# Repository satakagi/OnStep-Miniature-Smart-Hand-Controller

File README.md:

# OnStep-Miniature-Smart-Hand-Controller

## About
This is a much smaller design of the [Smart Hand Controller (SHC)](https://onstep.groups.io/g/main/wiki/7152) for [OnStep](https://onstep.groups.io/g/main)*1.
It is based on the [OnStep ESP32 Smart Hand Controller](https://baheyeldin.com/astronomy/onstep-esp32-smart-hand-controller-shc.html) circuit.

Therefore, the firmware is exactly the same as the ESP32 SHC, see the section Installing the Platform - For the ESP32 SHC on [The Smart Hand Controller (SHC)](https://onstep.groups.io/g/main/wiki/7152) page.

*1: OnStep is an open source GoTo motor drive for telescope mounts

## Parts List

* [DOIT ESP32 DEVKIT V1](https://www.amazon.com/s?k=DOIT+ESP32+DEVKIT+V1)
  * Note: Unlike the original ESP32 SHC, this design uses the DOIT ESP32 DEVKIT V1 with 30 pins.
* PCB ( refer to [kicad](kicad/) directory )
* [0.96" SSD1306 OLED Module](https://www.amazon.com/s?k=0.96+ssd1306+oled)
  * Note: Stick tape on the back side for insulation.
* Modular Jack 6P6C x 2
  * The plastic pins for fixing the jacks should be cut out.
* 7 Resistor Network (2K ohm)
* 4 Resistor Network (2K ohm)
* 2.54mm Header Pins 15pin F x 2, 4pin M, 2pin M 
* Momentary Tact Button Switches 0.2" x 0.24" x 7
  * Buttons would need to be at least 0.24" long.
* Case ( refer to [miniSHCcase.stl](miniSHCcase.stl) )
  * The example on this page were produced using the MSLA LCD 3d printer.

## Photos of the interior structure

Tape is attached to the back of the OLED module for insulation.
|  - |  -  |
| ---- | ---- |
|    |    |
|  <br>To avoid interference with the OLED, the leads protruding from the through-holes are trimmed.  |  <br>Attach a pad to the lid to hold the board in place and close the lid. (In this picture, the lid is fastened with tape.)   |

## License
This is licensed under the [TAPR Open Hardware License](https://tapr.org/the-tapr-open-hardware-license/), one of the well-known open-source hardware licenses.

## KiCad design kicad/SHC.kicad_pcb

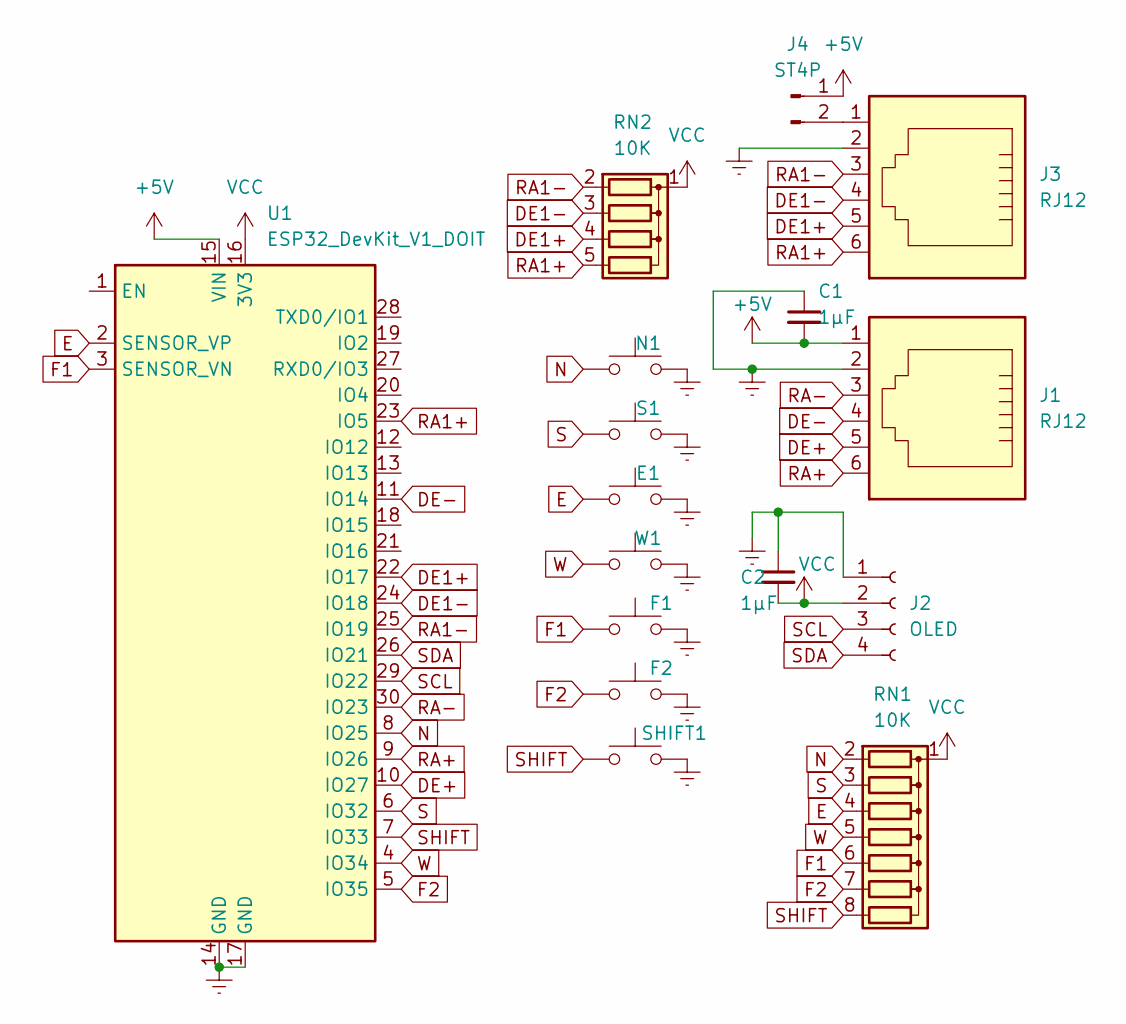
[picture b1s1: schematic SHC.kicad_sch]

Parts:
C1, C2: 1μF; C_Disc_D5.0mm_W2.5mm_P2.50mm
E1: SW_Push; SW_PUSH_6mm_H8mm
F1, F2: SW_Push; SW_PUSH_6mm_H8mm
J1, J3: RJ12; RJ25_Wayconn_MJEA-660X1_Horizontal_NoSupport
J2: OLED; PinHeader_1x04_P2.54mm_Vertical
J4: ST4P; PinHeader_1x02_P2.54mm_Vertical
N1: SW_Push; SW_PUSH_6mm_H8mm
RN1: 10K; R_Array_SIP8
RN2: 10K; R_Array_SIP5
S1: SW_Push; SW_PUSH_6mm_H8mm
SHIFT1: SW_Push; SW_PUSH_6mm_H8mm
U1: ESP32_DevKit_V1_DOIT; esp32_devkit_v1_doit
W1: SW_Push; SW_PUSH_6mm_H8mm

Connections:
+5V: C1.2, J1.1, J4.1, U1.15 (VIN)
DE1+: J3.5, RN2.4 (R3), U1.22 (IO17)
DE1-: J3.4, RN2.3 (R2), U1.24 (IO18)
DE+: J1.5, U1.10 (IO27)
DE-: J1.4, U1.11 (IO14)
E: E1.1, RN1.4 (R3), U1.2 (SENSOR_VP)
Earth: C1.1, C2.1, E1.2, F1.2, F2.2, J1.2, J2.1, J3.2, N1.2, S1.2, SHIFT1.2, U1.14 (GND), U1.17 (GND), W1.2; also elsewhere on the board
F1: F1.1, RN1.6 (R5), U1.3 (SENSOR_VN)
F2: F2.1, RN1.7 (R6), U1.5 (IO35)
N: N1.1, RN1.2 (R1), U1.8 (IO25)
unnamed: J3.1, J4.2
RA1+: J3.6, RN2.5 (R4), U1.23 (IO5)
RA1-: J3.3, RN2.2 (R1), U1.25 (IO19)
RA+: J1.6, U1.9 (IO26)
RA-: J1.3, U1.30 (IO23)
S: RN1.3 (R2), S1.1, U1.6 (IO32)
SCL: J2.3, U1.29 (IO22); also elsewhere on the board
SDA: J2.4, U1.26 (IO21); also elsewhere on the board
SHIFT: RN1.8 (R7), SHIFT1.1, U1.7 (IO33)
VCC: C2.2, J2.2, RN1.1 (common), RN2.1 (common), U1.16 (3V3); also elsewhere on the board
W: RN1.5 (R4), U1.4 (IO34), W1.1

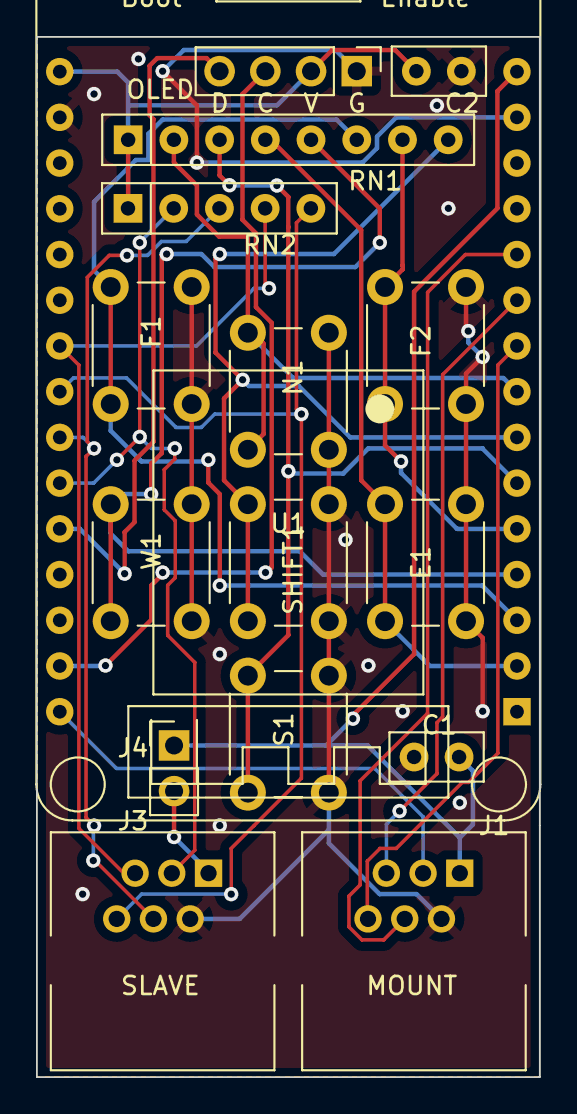
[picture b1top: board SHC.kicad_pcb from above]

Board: 2 copper layers, 27.9 x 57.8 mm, 16 parts (0 on the bottom side), 21 nets.

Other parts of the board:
OLED: OLED; PinHeader_1x04_P2.54mm_Vertical

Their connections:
Earth: OLED.1; also elsewhere on the board
SCL: OLED.3; also elsewhere on the board
SDA: OLED.4; also elsewhere on the board
VCC: OLED.2; also elsewhere on the board

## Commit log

2022-03-29 Create LICENSE
2022-03-29 Update LICENSE
